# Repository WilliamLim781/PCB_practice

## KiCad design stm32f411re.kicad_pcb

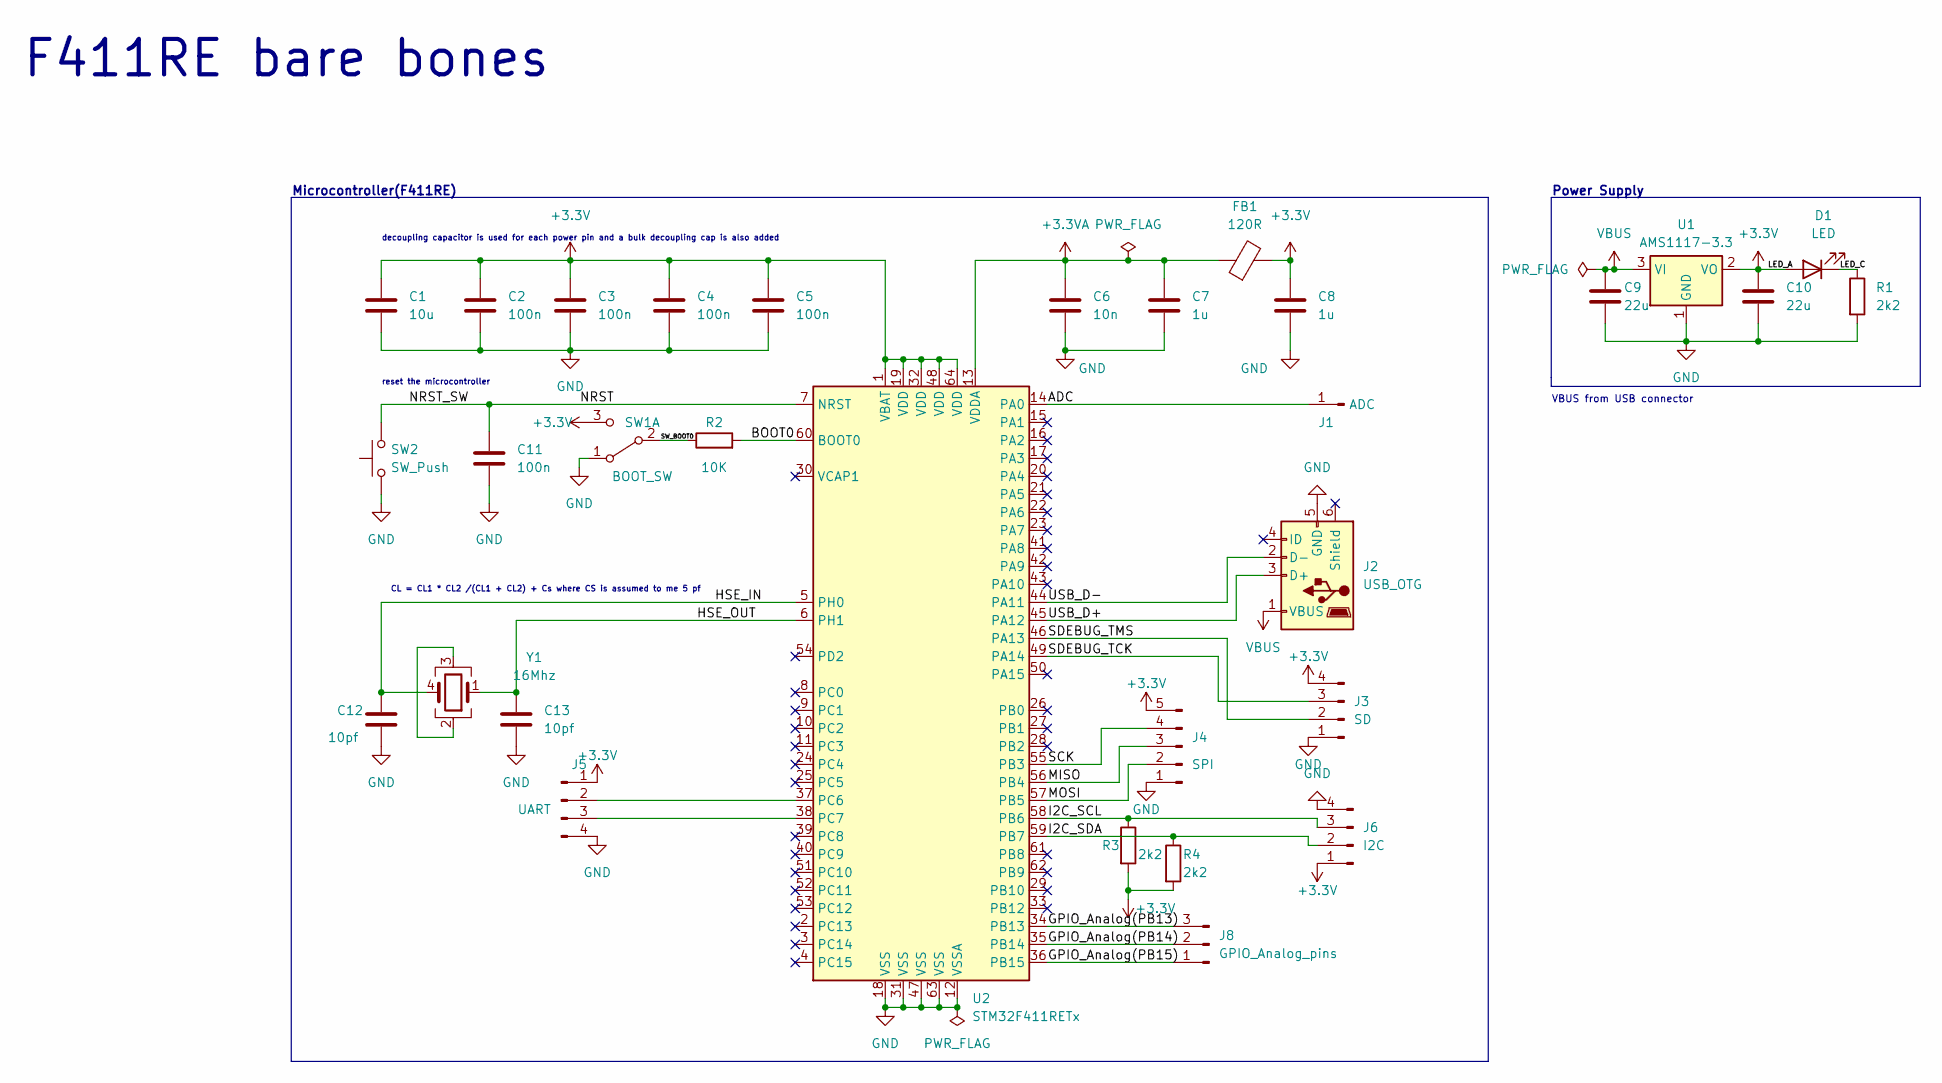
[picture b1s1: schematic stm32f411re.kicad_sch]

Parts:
C1: 10u; C_0603_1608Metric_Pad1.08x0.95mm_HandSolder
C2, C3, C4, C5, C11: 100n; C_0402_1005Metric_Pad0.74x0.62mm_HandSolder
C6: 10n; C_0402_1005Metric_Pad0.74x0.62mm_HandSolder
C7, C8: 1u; C_0402_1005Metric_Pad0.74x0.62mm_HandSolder
C9, C10: 22u; C_0805_2012Metric_Pad1.18x1.45mm_HandSolder
C12, C13: 10pf; C_0402_1005Metric_Pad0.74x0.62mm_HandSolder
D1: LED; LED_1210_3225Metric_Pad1.42x2.65mm_HandSolder
FB1: 120R; L_0603_1608Metric_Pad1.05x0.95mm_HandSolder
J1: ADC; PinHeader_1x01_P2.54mm_Vertical
J2: USB_OTG; USB_Micro-B_Wuerth_629105150521
J3: SD; PinHeader_1x04_P2.54mm_Vertical
J4: SPI; PinHeader_1x05_P2.54mm_Vertical
J5: UART; PinHeader_1x04_P2.54mm_Vertical
J6: I2C; PinHeader_1x04_P2.54mm_Vertical
J8: GPIO_Analog_pins; PinHeader_1x03_P2.54mm_Vertical
R1, R3, R4: 2k2; R_0402_1005Metric_Pad0.72x0.64mm_HandSolder
R2: 10K; R_0402_1005Metric_Pad0.72x0.64mm_HandSolder
SW1: BOOT_SW; SW_SPDT_PCM12
SW2: SW_Push; SW_SPST_B3U-1000P-B
U1: AMS1117-3.3; SOT-223-3_TabPin2
U2: STM32F411RETx; LQFP-64_10x10mm_P0.5mm
Y1: 16Mhz; Crystal_SMD_3225-4Pin_3.2x2.5mm_HandSoldering

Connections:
+3.3V: C1.1, C2.1, C3.1, C4.1, C5.1, C8.1, C10.1, D1.2 (A), FB1.2, J3.4, J4.5, J5.1, J6.1, R3.2, R4.2, SW1.3 (C), U1.2 (VO), U2.1 (VBAT), U2.19 (VDD), U2.32 (VDD), U2.48 (VDD), U2.64 (VDD)
+3.3VA: C6.1, C7.1, FB1.1, U2.13 (VDDA)
/ADC: J1.1, U2.14 (PA0)
/BOOT0: R2.2, U2.60 (BOOT0)
/GPIO_Analog(PB13): J8.3, U2.34 (PB13)
/GPIO_Analog(PB14): J8.2, U2.35 (PB14)
/GPIO_Analog(PB15): J8.1, U2.36 (PB15)
/HSE_IN: C12.2, U2.5 (PH0), Y1.4
/HSE_OUT: C13.2, U2.6 (PH1), Y1.1
/I2C_SCL: J6.3, R3.1, U2.58 (PB6)
/I2C_SDA: J6.2, R4.1, U2.59 (PB7)
/LED_C: D1.1 (K), R1.1
/MISO: J4.3, U2.56 (PB4)
/MOSI: J4.2, U2.57 (PB5)
/NRST: C11.1, SW2.2, U2.7 (NRST)
/SCK: J4.4, U2.55 (PB3)
/SDEBUG_TCK: J3.3, U2.49 (PA14)
/SDEBUG_TMS: J3.2, U2.46 (PA13)
/SW_BOOT0: R2.1, SW1.2 (B)
/USB_D+: J2.3 (D+), U2.45 (PA12)
/USB_D-: J2.2 (D-), U2.44 (PA11)
GND: C1.2, C2.2, C3.2, C4.2, C5.2, C6.2, C7.2, C8.2, C9.2, C10.2, C11.2, C12.1, C13.1, J2.5 (GND), J3.1, J4.1, J5.4, J6.4, R1.2, SW1.1 (A), SW2.1, U1.1 (GND), U2.12 (VSSA), U2.18 (VSS), U2.31 (VSS), U2.47 (VSS), U2.63 (VSS)
unnamed: J5.2, U2.37 (PC6)
unnamed: J5.3, U2.38 (PC7)
unnamed: Y1.2, Y1.3
VBUS: C9.1, J2.1 (VBUS), U1.3 (VI)

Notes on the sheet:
decoupling capacitor is used for each power pin and a bulk decoupling cap is also added
Power Supply
reset the microcontroller
VBUS from USB connector
F411RE bare bones
Microcontroller(F411RE)
CL = CL1 * CL2 /(CL1 + CL2) + Cs where CS is assumed to me 5 pf

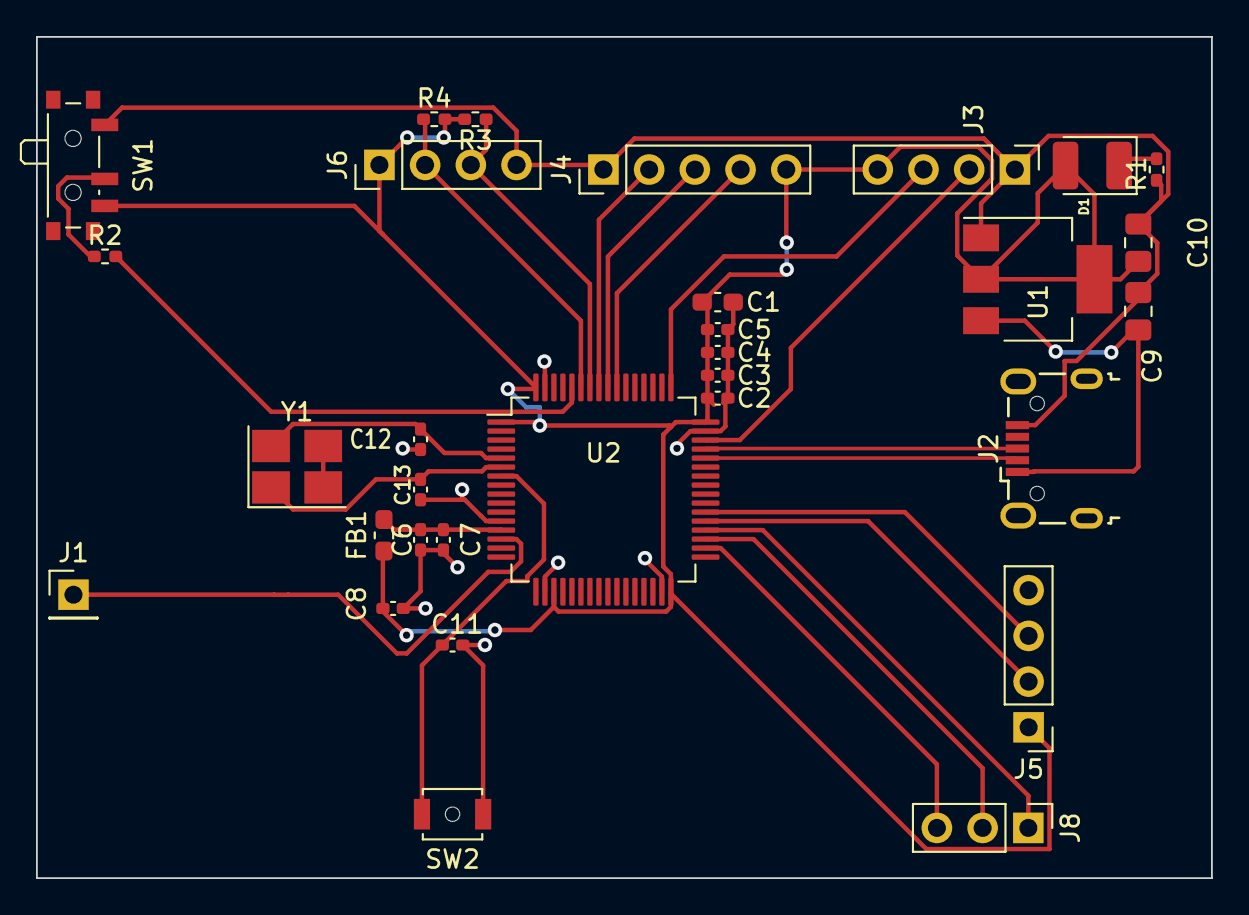
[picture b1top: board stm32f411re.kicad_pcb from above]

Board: 2 copper layers, 65.3 x 46.7 mm, 31 parts (0 on the bottom side), 26 nets.

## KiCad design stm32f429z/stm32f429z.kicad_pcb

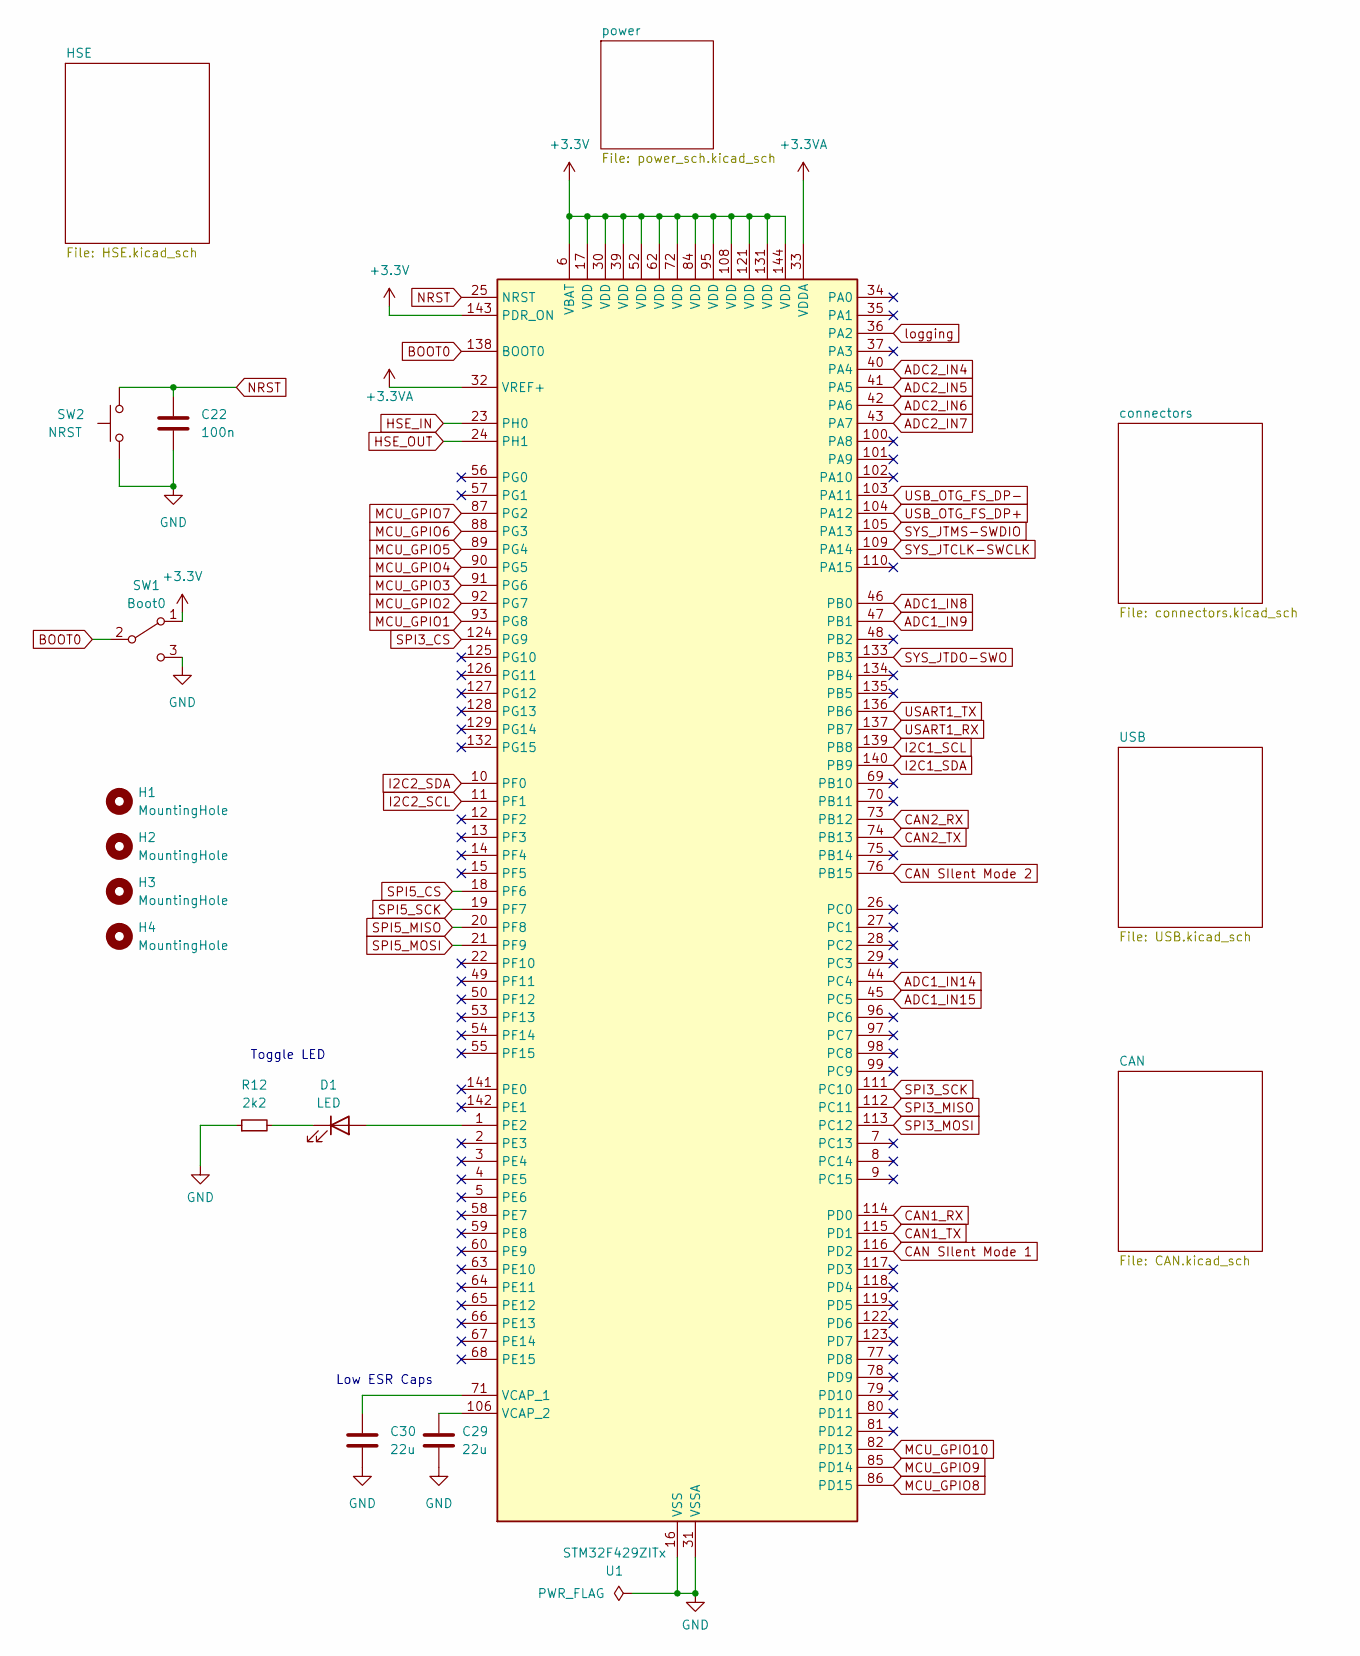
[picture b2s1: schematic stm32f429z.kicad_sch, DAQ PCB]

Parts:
C22: 100n; C_0603_1608Metric_Pad1.08x0.95mm_HandSolder; JLCpart# C76599
C29, C30: 22u; C_0603_1608Metric_Pad1.08x0.95mm_HandSolder; JLCpart# C96446
D1: LED; LED_0603_1608Metric_Pad1.05x0.95mm_HandSolder; JLCpart# C72038
H1, H2, H3, H4: MountingHole; MountingHole_4.3mm_M4_Pad_Via
R12: 2k2; R_0603_1608Metric_Pad0.98x0.95mm_HandSolder; JLCpart# C427273
SW1: Boot0; SW_SPDT_CK-JS102011SAQN
SW2: NRST; SW_SPST_PTS645
U1: STM32F429ZITx; LQFP-144_20x20mm_P0.5mm; JLCpart# C92002

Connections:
ADC1_IN8: U1.46 (PB0); also elsewhere on the board
ADC1_IN9: U1.47 (PB1); also elsewhere on the board
ADC1_IN14: U1.44 (PC4); also elsewhere on the board
ADC1_IN15: U1.45 (PC5); also elsewhere on the board
ADC2_IN4: U1.40 (PA4); also elsewhere on the board
ADC2_IN5: U1.41 (PA5); also elsewhere on the board
ADC2_IN6: U1.42 (PA6); also elsewhere on the board
ADC2_IN7: U1.43 (PA7); also elsewhere on the board
BOOT0: SW1.2 (B), U1.138 (BOOT0)
CAN1_RX: U1.114 (PD0); also elsewhere on the board
CAN2_RX: U1.73 (PB12); also elsewhere on the board
CAN2_TX: U1.74 (PB13); also elsewhere on the board
CAN SIlent Mode 1: U1.116 (PD2); also elsewhere on the board
CAN SIlent Mode 2: U1.76 (PB15); also elsewhere on the board
HSE_IN: U1.23 (PH0); also elsewhere on the board
HSE_OUT: U1.24 (PH1); also elsewhere on the board
I2C1_SCL: U1.139 (PB8); also elsewhere on the board
I2C1_SDA: U1.140 (PB9); also elsewhere on the board
I2C2_SCL: U1.11 (PF1); also elsewhere on the board
I2C2_SDA: U1.10 (PF0); also elsewhere on the board
MCU_GPIO1: U1.93 (PG8); also elsewhere on the board
MCU_GPIO2: U1.92 (PG7); also elsewhere on the board
MCU_GPIO3: U1.91 (PG6); also elsewhere on the board
MCU_GPIO4: U1.90 (PG5); also elsewhere on the board
MCU_GPIO5: U1.89 (PG4); also elsewhere on the board
MCU_GPIO6: U1.88 (PG3); also elsewhere on the board
MCU_GPIO7: U1.87 (PG2); also elsewhere on the board
MCU_GPIO8: U1.86 (PD15); also elsewhere on the board
MCU_GPIO9: U1.85 (PD14); also elsewhere on the board
MCU_GPIO10: U1.82 (PD13); also elsewhere on the board
unnamed: C30.1, U1.71 (VCAP_1)
unnamed: C29.1, U1.106 (VCAP_2)
SPI3_CS: U1.124 (PG9); also elsewhere on the board
SPI3_MISO: U1.112 (PC11); also elsewhere on the board
SPI3_MOSI: U1.113 (PC12); also elsewhere on the board
SPI3_SCK: U1.111 (PC10); also elsewhere on the board
SPI5_CS: U1.18 (PF6); also elsewhere on the board
SPI5_MISO: U1.20 (PF8); also elsewhere on the board
SPI5_MOSI: U1.21 (PF9); also elsewhere on the board
SPI5_SCK: U1.19 (PF7); also elsewhere on the board
SYS_JTCLK-SWCLK: U1.109 (PA14); also elsewhere on the board
SYS_JTDO-SWO: U1.133 (PB3); also elsewhere on the board
SYS_JTMS-SWDIO: U1.105 (PA13); also elsewhere on the board
USART1_RX: U1.137 (PB7); also elsewhere on the board
USART1_TX: U1.136 (PB6); also elsewhere on the board
USB_OTG_FS_DP+: U1.104 (PA12); also elsewhere on the board
USB_OTG_FS_DP-: U1.103 (PA11); also elsewhere on the board

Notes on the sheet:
Toggle LED
Low ESR Caps

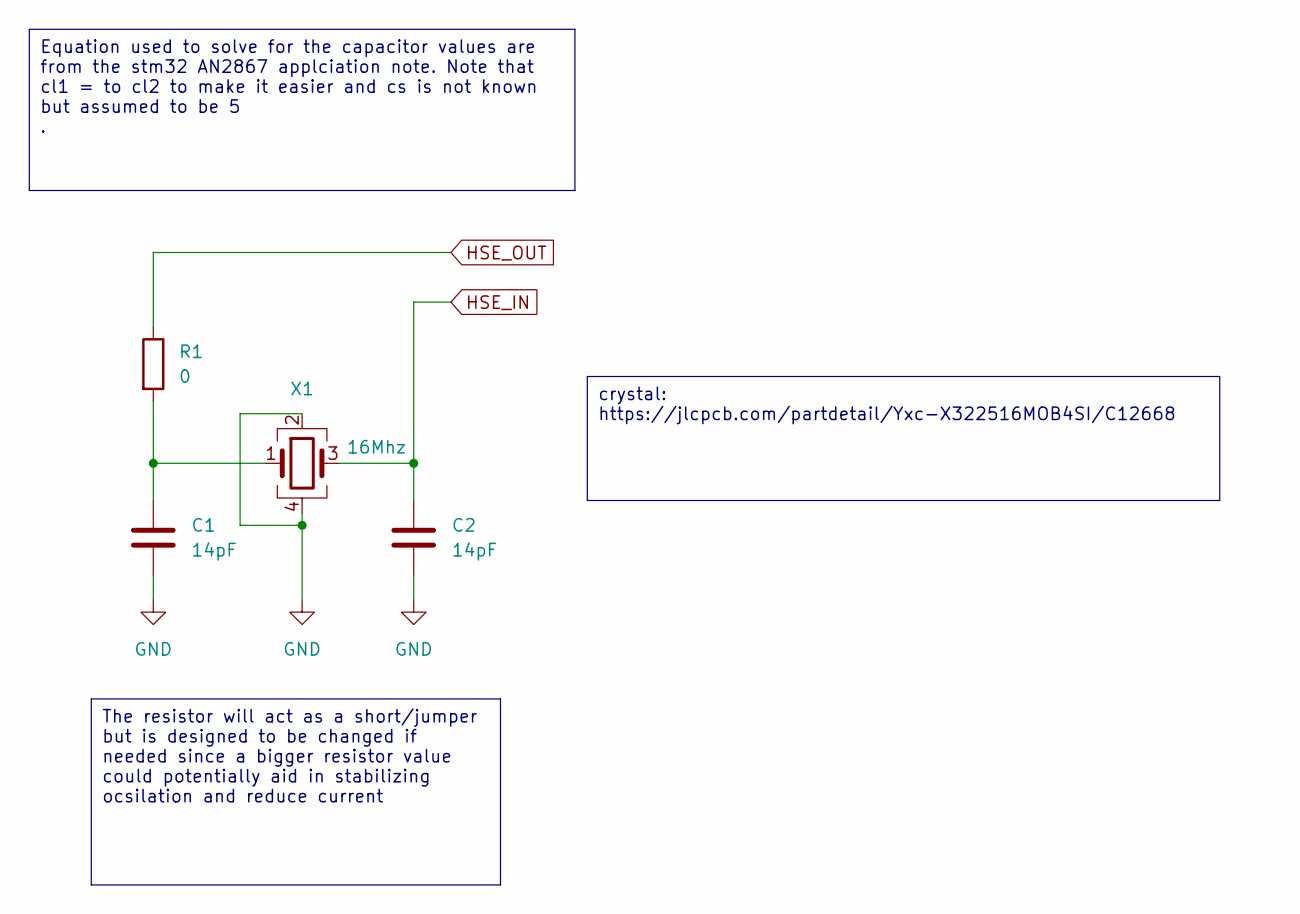
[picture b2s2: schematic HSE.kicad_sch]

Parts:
C1, C2: 14pF; C_0603_1608Metric_Pad1.08x0.95mm_HandSolder; JLCpart# C5360816
R1: 0; R_0603_1608Metric_Pad0.98x0.95mm_HandSolder
X1: 16Mhz; Crystal_SMD_3225-4Pin_3.2x2.5mm_HandSoldering; JLCpart# C12668

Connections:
HSE_IN: C2.1, X1.3; also elsewhere on the board
HSE_OUT: R1.1; also elsewhere on the board
unnamed: C1.1, R1.2, X1.1

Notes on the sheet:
Equation used to solve for the capacitor values are from the stm32 AN2867 applciation note. Note that cl1 = to cl2 to make it easier and cs is not known but assumed to be 5 .
The resistor will act as a short/jumper but is designed to be changed if needed since a bigger resistor value could potentially aid in stabilizing ocsilation and reduce current
crystal: https://jlcpcb.com/partdetail/Yxc-X322516MOB4SI/C12668

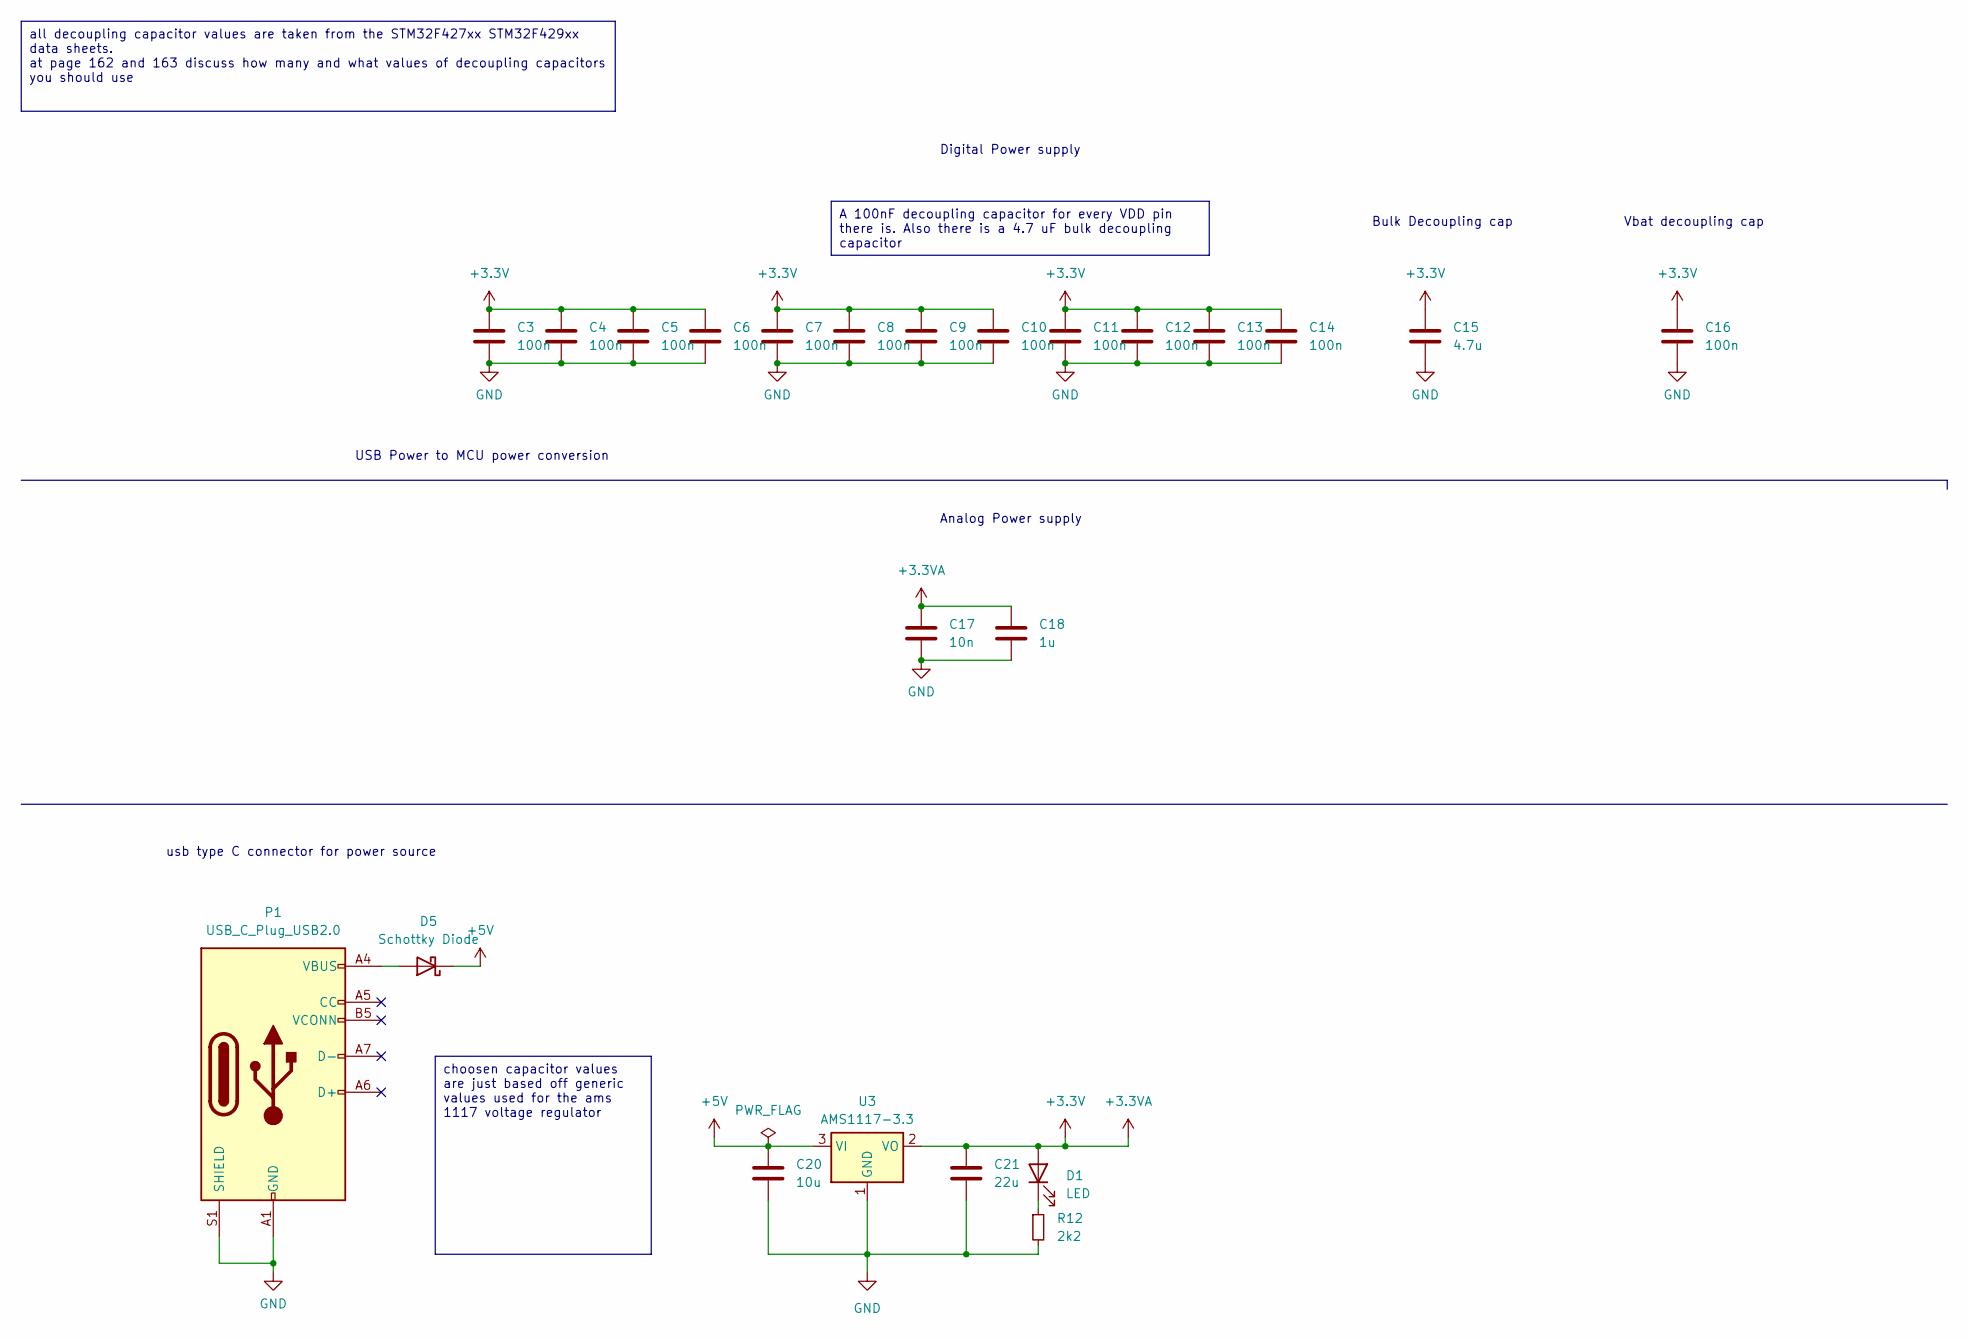
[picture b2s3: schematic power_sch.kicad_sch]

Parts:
C3, C4, C5, C6, C7, C8, C9, C10, C11, C12, C13, C14, C16: 100n; C_0603_1608Metric_Pad1.08x0.95mm_HandSolder; JLCpart# C76599
C15: 4.7u; C_0603_1608Metric_Pad1.08x0.95mm_HandSolder; JLCpart# C19666
C17: 10n; C_0603_1608Metric_Pad1.08x0.95mm_HandSolder; JLCpart# C57112
C18: 1u; C_0603_1608Metric_Pad1.08x0.95mm_HandSolder; JLCpart# C15849
C20: 10u; C_0603_1608Metric_Pad1.08x0.95mm_HandSolder; JLCpart# C96446
C21: 22u; C_0603_1608Metric_Pad1.08x0.95mm_HandSolder; JLCpart# C96446
D1: LED; LED_0603_1608Metric_Pad1.05x0.95mm_HandSolder; JLCpart# C72038
D5: Schottky Diode; D_SMA-SMB_Universal_Handsoldering; JLCpart# C2480
P1: USB_C_Plug_USB2.0; USB_C_Receptacle_GCT_USB4085
R12: 2k2; R_0603_1608Metric_Pad0.98x0.95mm_HandSolder; JLCpart# C427273
U3: AMS1117-3.3; SOT-223-3_TabPin2

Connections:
unnamed 47: D5.2 (A); also elsewhere on the board

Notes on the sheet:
all decoupling capacitor values are taken from the STM32F427xx STM32F429xx data sheets. at page 162 and 163 discuss how many and what values of decoupling capacitors you should use
choosen capacitor values are just based off generic values used for the ams 1117 voltage regulator
A 100nF decoupling capacitor for every VDD pin there is. Also there is a 4.7 uF bulk decoupling capacitor
Vbat decoupling cap
usb type C connector for power source
Bulk Decoupling cap
USB Power to MCU power conversion
Digital Power supply
Analog Power supply

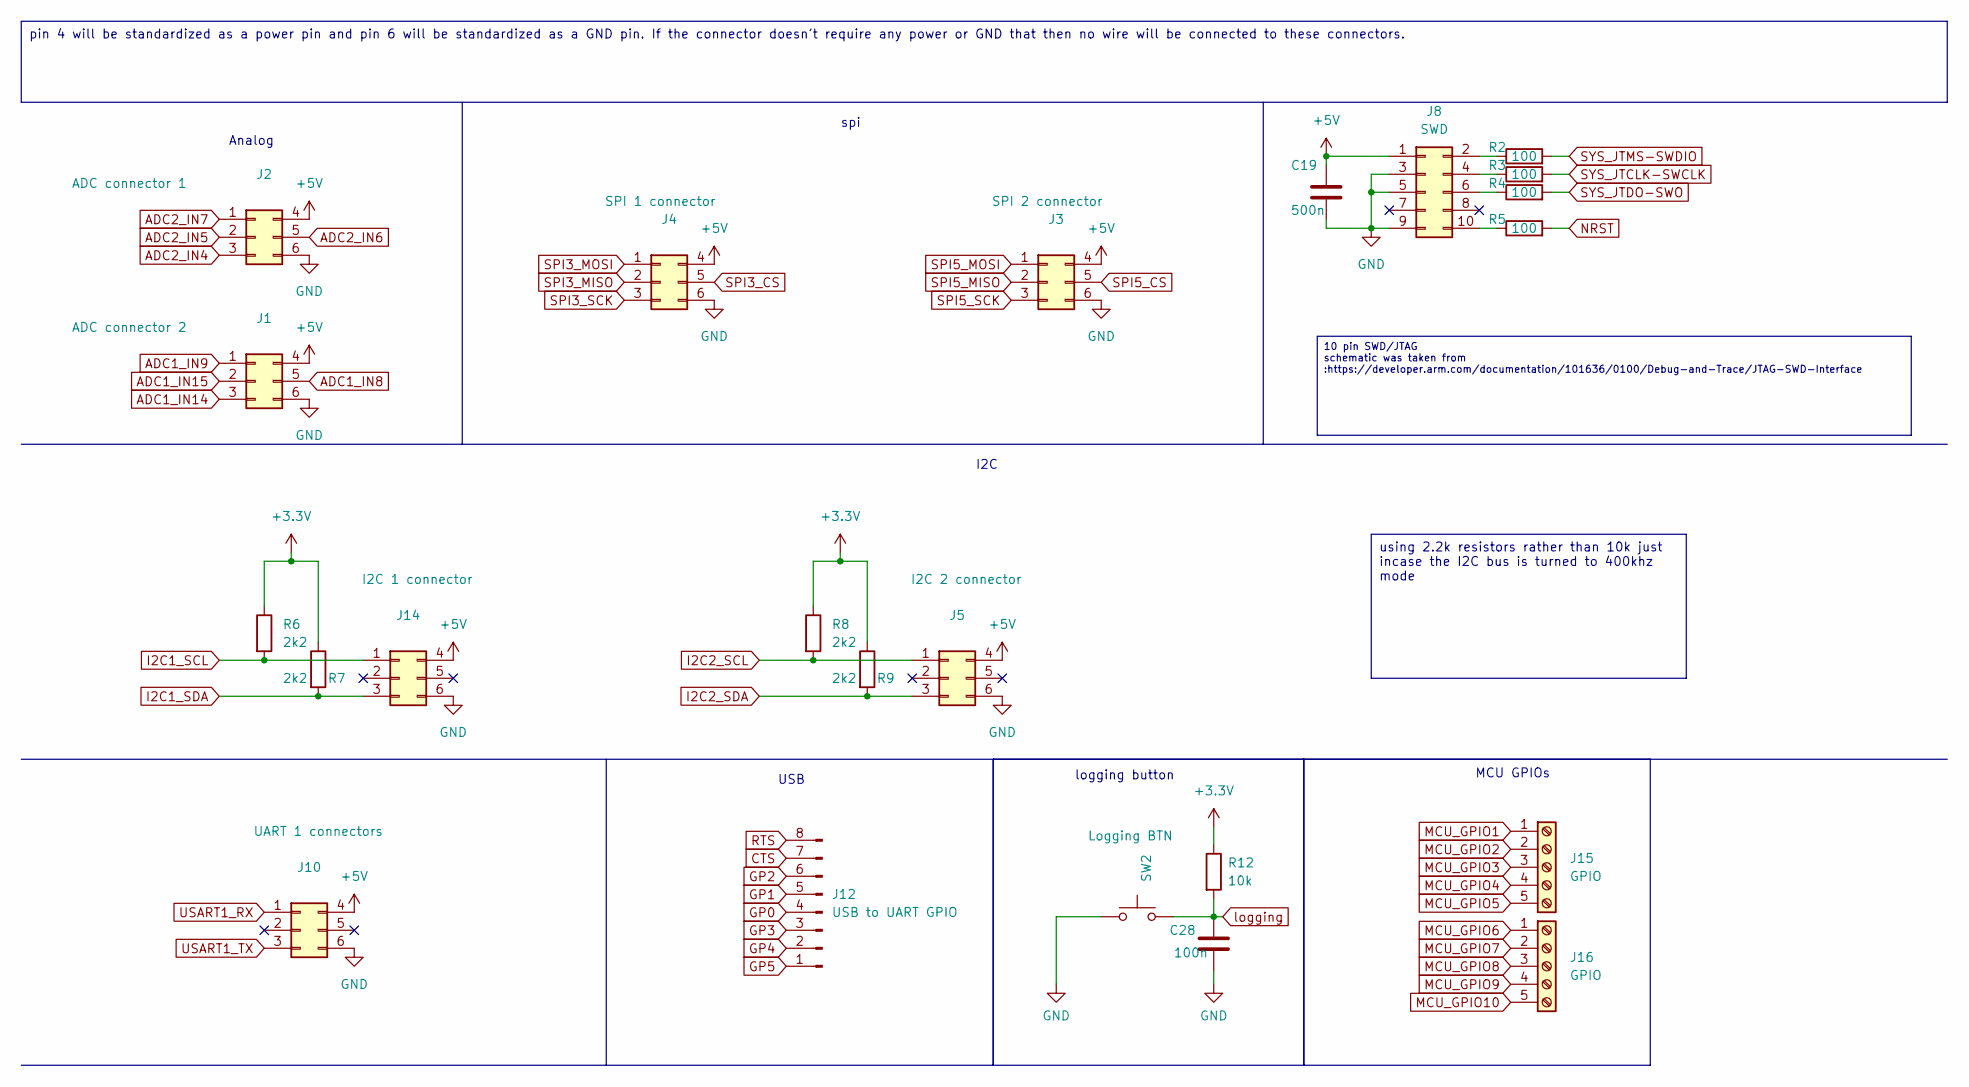
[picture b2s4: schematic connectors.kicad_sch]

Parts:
C19: 500n; C_0603_1608Metric_Pad1.08x0.95mm_HandSolder; JLCpart# C124567
C28: 100n; C_0603_1608Metric_Pad1.08x0.95mm_HandSolder; JLCpart# C76599
J1: ADC connector 2; Molex_MegaFit_2x03x5.70mm_Angled
J2: ADC connector 1; Molex_MegaFit_2x03x5.70mm_Angled
J3: SPI 2 connector; Molex_MegaFit_2x03x5.70mm_Angled
J4: SPI 1 connector; Molex_MegaFit_2x03x5.70mm_Angled
J5: I2C 2 connector; Molex_MegaFit_2x03x5.70mm_Angled
J8: SWD; PinHeader_2x05_P2.54mm_Vertical
J10: UART 1 connectors; Molex_MegaFit_2x03x5.70mm_Angled
J12: USB to UART GPIO; PinHeader_1x08_P2.54mm_Vertical
J14: I2C 1 connector; Molex_MegaFit_2x03x5.70mm_Angled
J15, J16: GPIO; TerminalBlock_Phoenix_MKDS-1,5-5_1x05_P5.00mm_Horizontal
R2, R3, R4, R5: 100; R_0603_1608Metric_Pad0.98x0.95mm_HandSolder; JLCpart# C441885
R6, R7, R8, R9: 2k2; R_0603_1608Metric_Pad0.98x0.95mm_HandSolder; JLCpart# C427273
R12: 10k; R_0603_1608Metric_Pad0.98x0.95mm_HandSolder; JLCpart# C4226066
SW2: Logging BTN; SW_SPST_PTS645

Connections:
ADC1_IN8: J1.5; also elsewhere on the board
ADC1_IN9: J1.1; also elsewhere on the board
ADC1_IN14: J1.3; also elsewhere on the board
ADC1_IN15: J1.2; also elsewhere on the board
ADC2_IN4: J2.3; also elsewhere on the board
ADC2_IN5: J2.2; also elsewhere on the board
ADC2_IN6: J2.5; also elsewhere on the board
ADC2_IN7: J2.1; also elsewhere on the board
CTS: J12.7; also elsewhere on the board
GP0: J12.4; also elsewhere on the board
GP1: J12.5; also elsewhere on the board
GP2: J12.6; also elsewhere on the board
GP3: J12.3; also elsewhere on the board
GP4: J12.2; also elsewhere on the board
GP5: J12.1; also elsewhere on the board
I2C1_SCL: J14.1, R6.2; also elsewhere on the board
I2C1_SDA: J14.3, R7.2; also elsewhere on the board
I2C2_SCL: J5.1, R8.2; also elsewhere on the board
I2C2_SDA: J5.3, R9.2; also elsewhere on the board
MCU_GPIO1: J15.1; also elsewhere on the board
MCU_GPIO2: J15.2; also elsewhere on the board
MCU_GPIO3: J15.3; also elsewhere on the board
MCU_GPIO4: J15.4; also elsewhere on the board
MCU_GPIO5: J15.5; also elsewhere on the board
MCU_GPIO6: J16.1; also elsewhere on the board
MCU_GPIO7: J16.2; also elsewhere on the board
MCU_GPIO8: J16.3; also elsewhere on the board
MCU_GPIO9: J16.4; also elsewhere on the board
MCU_GPIO10: J16.5; also elsewhere on the board
unnamed: J8.2, R2.1
unnamed: J8.4, R3.1
unnamed: J8.6, R4.1
unnamed: J8.10, R5.1
RTS: J12.8; also elsewhere on the board
SPI3_CS: J4.5; also elsewhere on the board
SPI3_MISO: J4.2; also elsewhere on the board
SPI3_MOSI: J4.1; also elsewhere on the board
SPI3_SCK: J4.3; also elsewhere on the board
SPI5_CS: J3.5; also elsewhere on the board
SPI5_MISO: J3.2; also elsewhere on the board
SPI5_MOSI: J3.1; also elsewhere on the board
SPI5_SCK: J3.3; also elsewhere on the board
SYS_JTCLK-SWCLK: R3.2; also elsewhere on the board
SYS_JTDO-SWO: R4.2; also elsewhere on the board
SYS_JTMS-SWDIO: R2.2; also elsewhere on the board
USART1_RX: J10.1; also elsewhere on the board
USART1_TX: J10.3; also elsewhere on the board

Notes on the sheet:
pin 4 will be standardized as a power pin and pin 6 will be standardized as a GND pin. If the connector doesn't require any power or GND that then no wire will be connected to these connectors.
10 pin SWD/JTAG schematic was taken from :https://developer.arm.com/documentation/101636/0100/Debug-and-Trace/JTAG-SWD-Interface
using 2.2k resistors rather than 10k just incase the I2C bus is turned to 400khz mode
Analog
spi
I2C
USB
logging button
MCU GPIOs

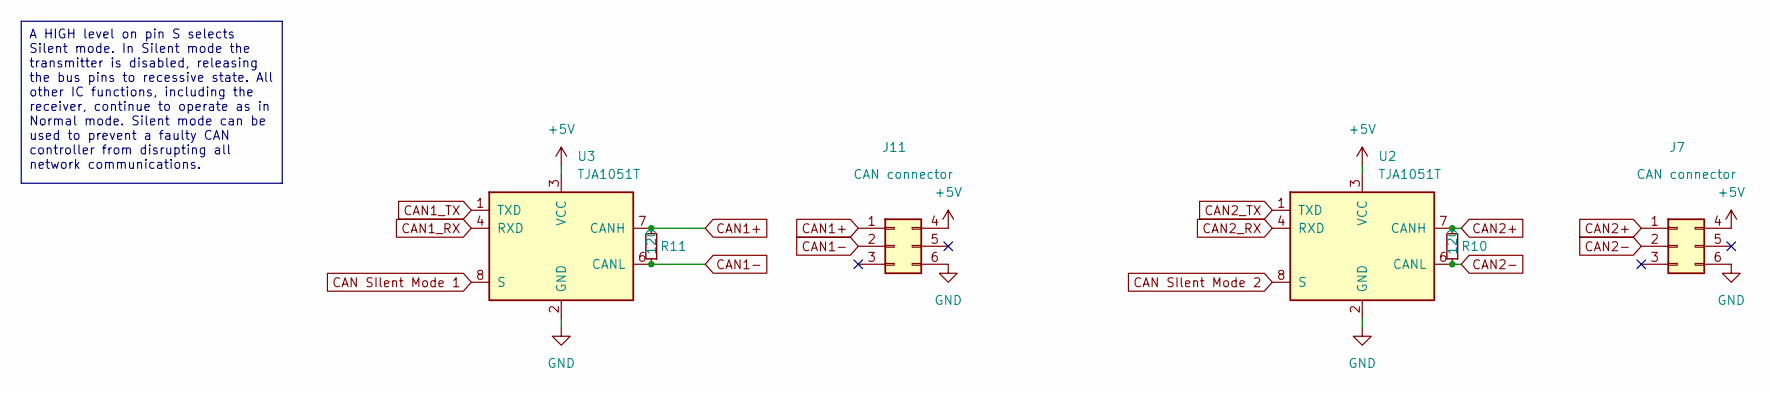
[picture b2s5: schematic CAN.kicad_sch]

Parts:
J7, J11: CAN connector; Molex_MegaFit_2x03x5.70mm_Angled
R10, R11: 120; R_0603_1608Metric_Pad0.98x0.95mm_HandSolder; JLCpart# C2906988
U2, U3: TJA1051T; SOIC-8_3.9x4.9mm_P1.27mm; JLCpart# C38695

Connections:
CAN1+: J11.1, R11.2, U3.7 (CANH)
CAN1-: J11.2, R11.1, U3.6 (CANL)
CAN1_RX: U3.4 (RXD); also elsewhere on the board
CAN2+: J7.1, R10.2, U2.7 (CANH)
CAN2-: J7.2, R10.1, U2.6 (CANL)
CAN2_RX: U2.4 (RXD); also elsewhere on the board
CAN2_TX: U2.1 (TXD); also elsewhere on the board
CAN SIlent Mode 1: U3.8 (S); also elsewhere on the board
CAN SIlent Mode 2: U2.8 (S); also elsewhere on the board

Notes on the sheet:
A HIGH level on pin S selects Silent mode. In Silent mode the transmitter is disabled, releasing the bus pins to recessive state. All other IC functions, including the receiver, continue to operate as in Normal mode. Silent mode can be used to prevent a faulty CAN controller from disrupting all net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

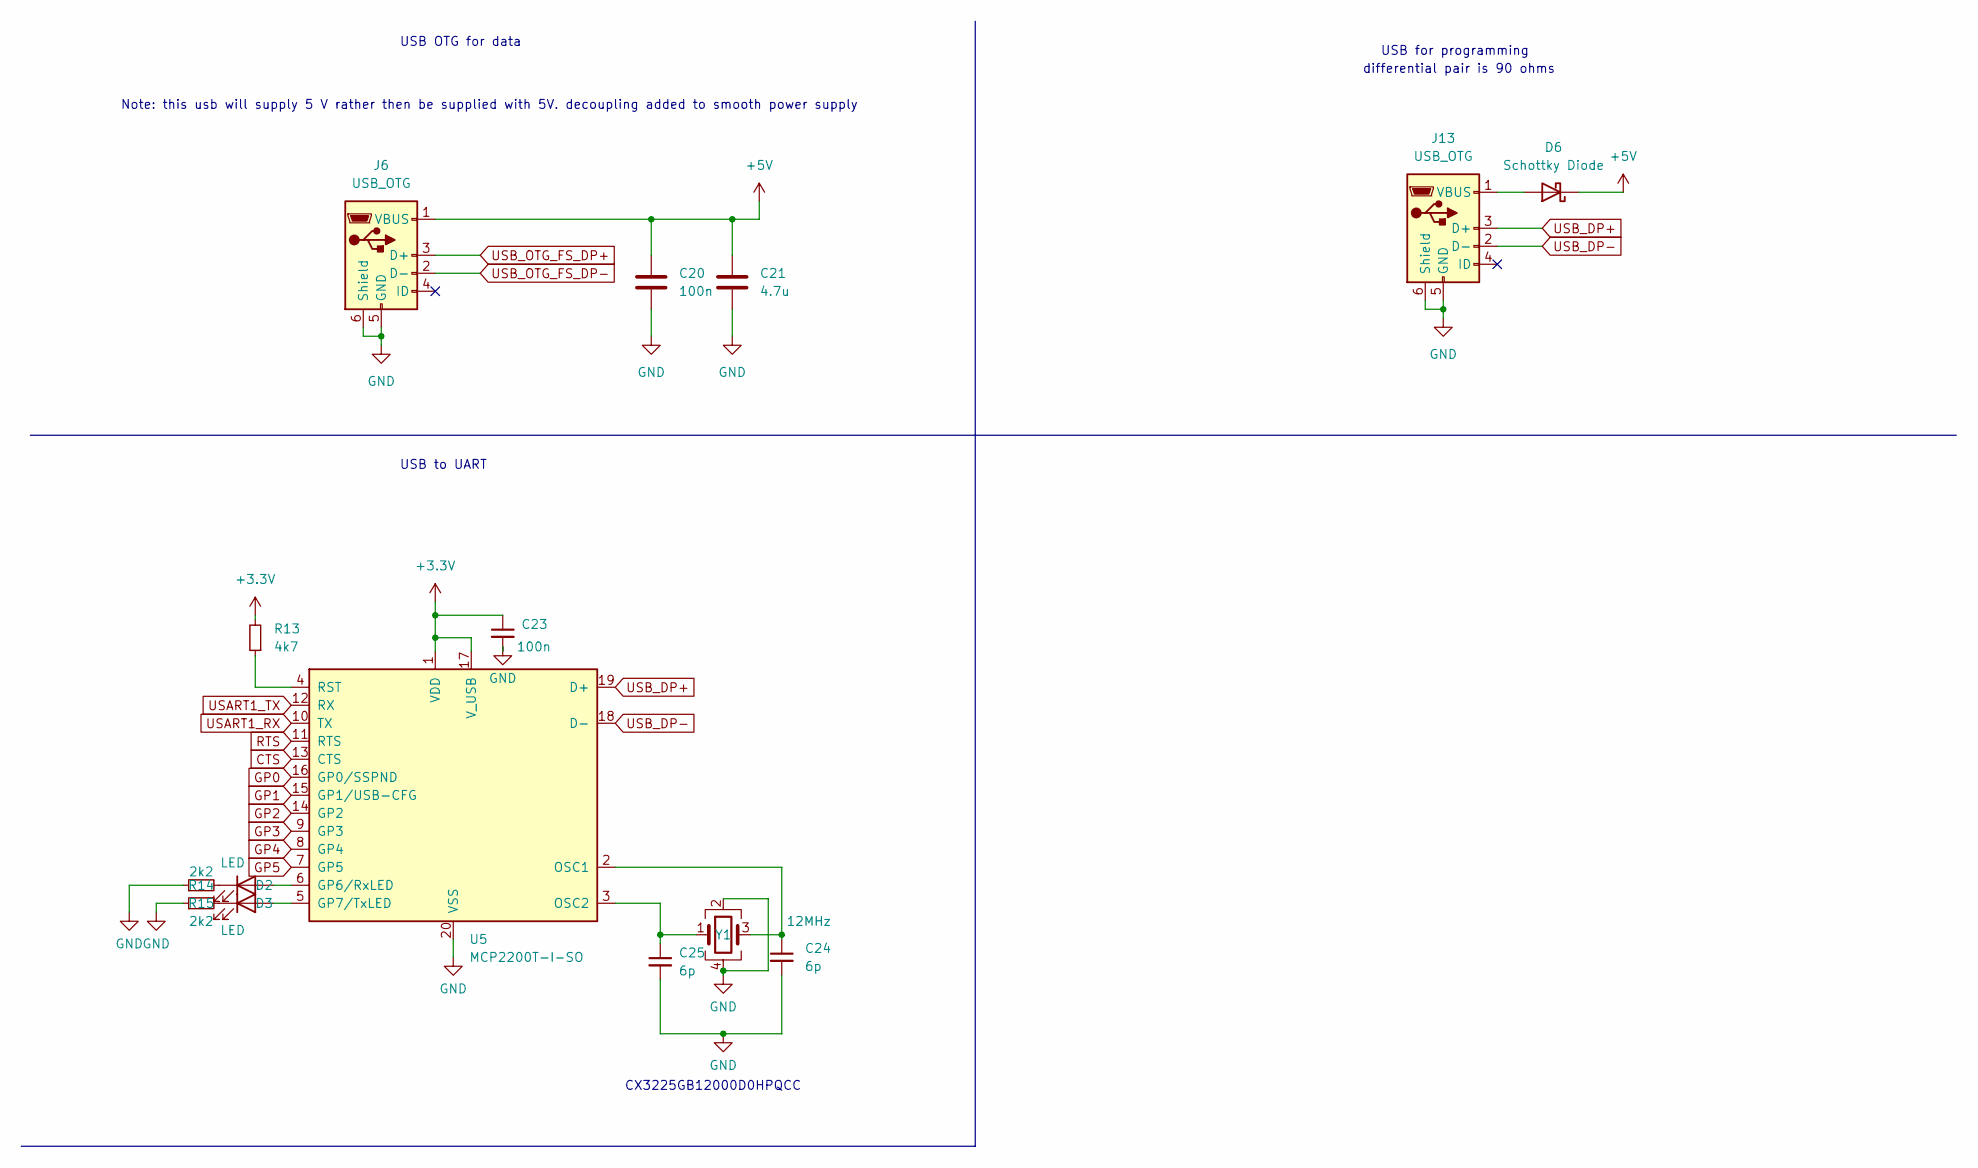
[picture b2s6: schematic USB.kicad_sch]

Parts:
C20, C23: 100n; C_0603_1608Metric_Pad1.08x0.95mm_HandSolder; JLCpart# C76599
C21: 4.7u; C_0603_1608Metric_Pad1.08x0.95mm_HandSolder; JLCpart# C19666
C24, C25: 6p; C_0603_1608Metric_Pad1.08x0.95mm_HandSolder; JLCpart# C282508
D2, D3: LED; LED_0603_1608Metric_Pad1.05x0.95mm_HandSolder; JLCpart# C72038
D6: Schottky Diode; D_SMA-SMB_Universal_Handsoldering; JLCpart# C2480
J6: USB_OTG; USB_A_Wuerth_61400826021_Horizontal_Stacked
J13: USB_OTG; USB_Mini-B_Wuerth_65100516121_Horizontal
R13: 4k7; R_0603_1608Metric_Pad0.98x0.95mm_HandSolder; JLCpart# C473239
R14, R15: 2k2; R_0603_1608Metric_Pad0.98x0.95mm_HandSolder; JLCpart# C427273
U5: MCP2200T-I-SO; SOIC-20W_7.5x12.8mm_P1.27mm
Y1: 12MHz; Crystal_SMD_3225-4Pin_3.2x2.5mm_HandSoldering

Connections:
CTS: U5.13 (CTS); also elsewhere on the board
GP0: U5.16 (GP0/SSPND); also elsewhere on the board
GP1: U5.15 (GP1/USB-CFG); also elsewhere on the board
GP2: U5.14 (GP2); also elsewhere on the board
GP3: U5.9 (GP3); also elsewhere on the board
GP4: U5.8 (GP4); also elsewhere on the board
GP5: U5.7 (GP5); also elsewhere on the board
unnamed: D2.2 (A), U5.6 (GP6/RxLED)
unnamed: D2.1 (K), R14.2
unnamed: D3.2 (A), U5.5 (GP7/TxLED)
unnamed: D3.1 (K), R15.2
unnamed: D6.2 (A), J13.1 (VBUS)
unnamed: C24.1, U5.2 (OSC1), Y1.3
unnamed: C25.1, U5.3 (OSC2), Y1.1
unnamed: R13.1, U5.4 (RST)
RTS: U5.11 (RTS); also elsewhere on the board
USART1_RX: U5.10 (TX); also elsewhere on the board
USART1_TX: U5.12 (RX); also elsewhere on the board
USB_DP+: J13.3 (D+), U5.19 (D+)
USB_DP-: J13.2 (D-), U5.18 (D-)

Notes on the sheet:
differential pair is 90 ohms
USB OTG for data
USB to UART
Note: this usb will supply 5 V rather then be supplied with 5V. decoupling added to smooth power supply
CX3225GB12000D0HPQCC
USB for programming

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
